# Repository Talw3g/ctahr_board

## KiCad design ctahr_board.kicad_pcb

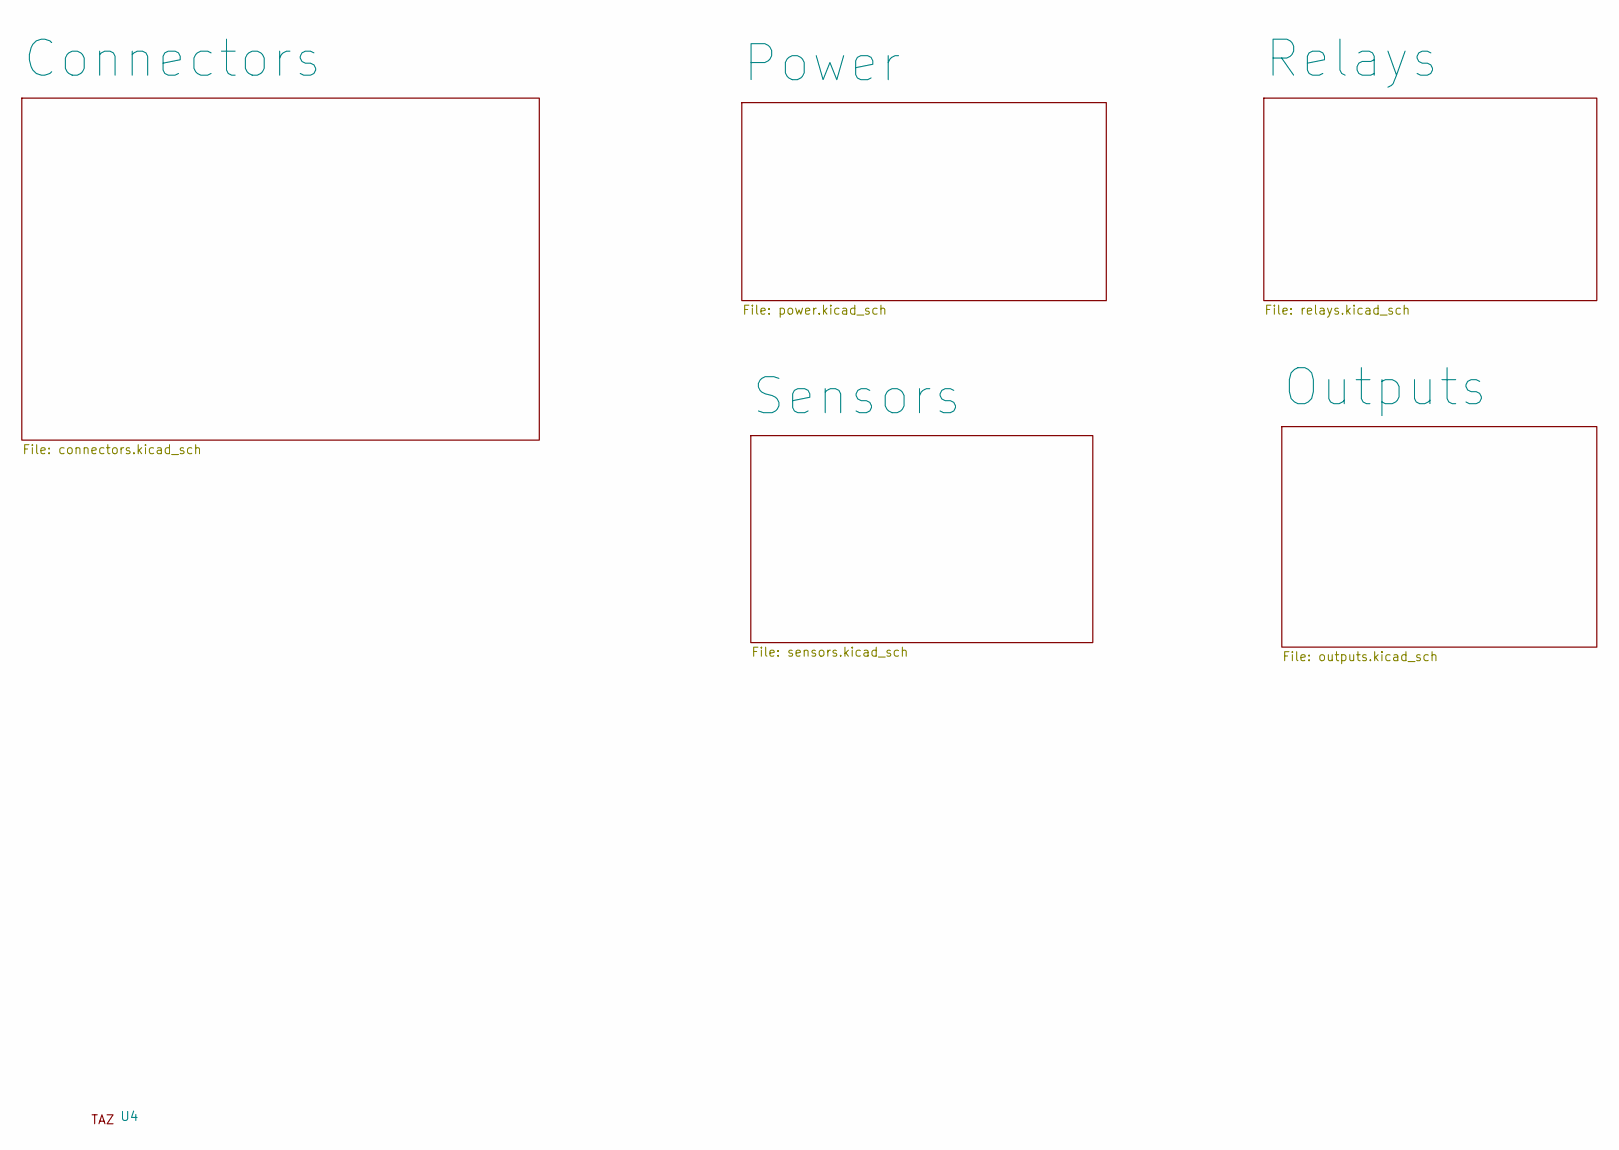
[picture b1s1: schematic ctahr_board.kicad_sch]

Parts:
U4: taz

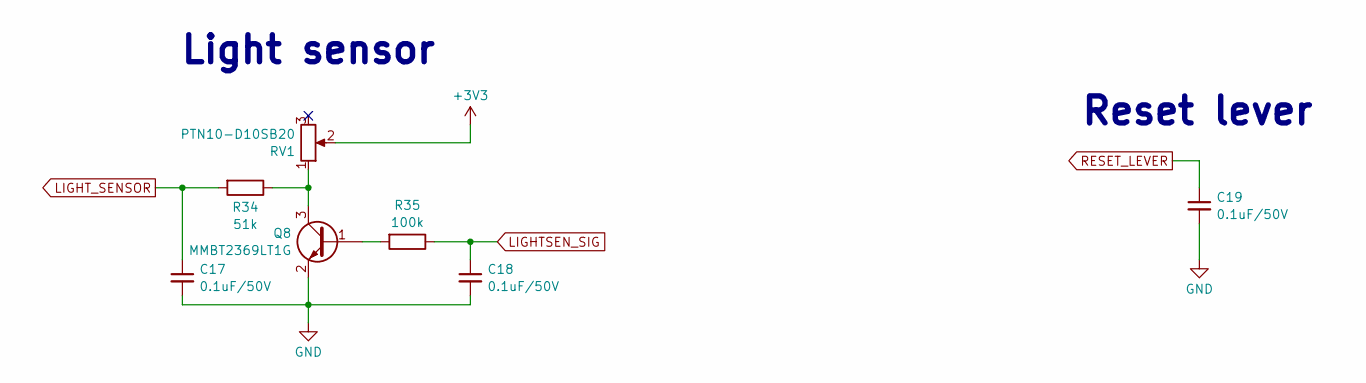
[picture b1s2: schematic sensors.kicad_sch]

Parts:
C17, C18, C19: 0.1uF/50V; C_0603_1608Metric_Pad1.08x0.95mm_HandSolder
Q8: MMBT2369LT1G; SOT-23_Handsoldering
R34: 51k; R_0603_1608Metric_Pad0.98x0.95mm_HandSolder
R35: 100k; R_0603_1608Metric_Pad0.98x0.95mm_HandSolder
RV1: PTN10-D10SB20; TRIM_PTN10-D10SB20

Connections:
+3V3: RV1.2; also elsewhere on the board
GND: C17.2, C18.2, C19.2, Q8.2 (E); also elsewhere on the board
LIGHTSEN_SIG: C18.1, R35.1; also elsewhere on the board
LIGHT_SENSOR: C17.1, R34.2; also elsewhere on the board
unnamed: Q8.1 (B), R35.2
unnamed: Q8.3 (C), R34.1, RV1.1
RESET_LEVER: C19.1; also elsewhere on the board

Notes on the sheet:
Reset lever
Light sensor

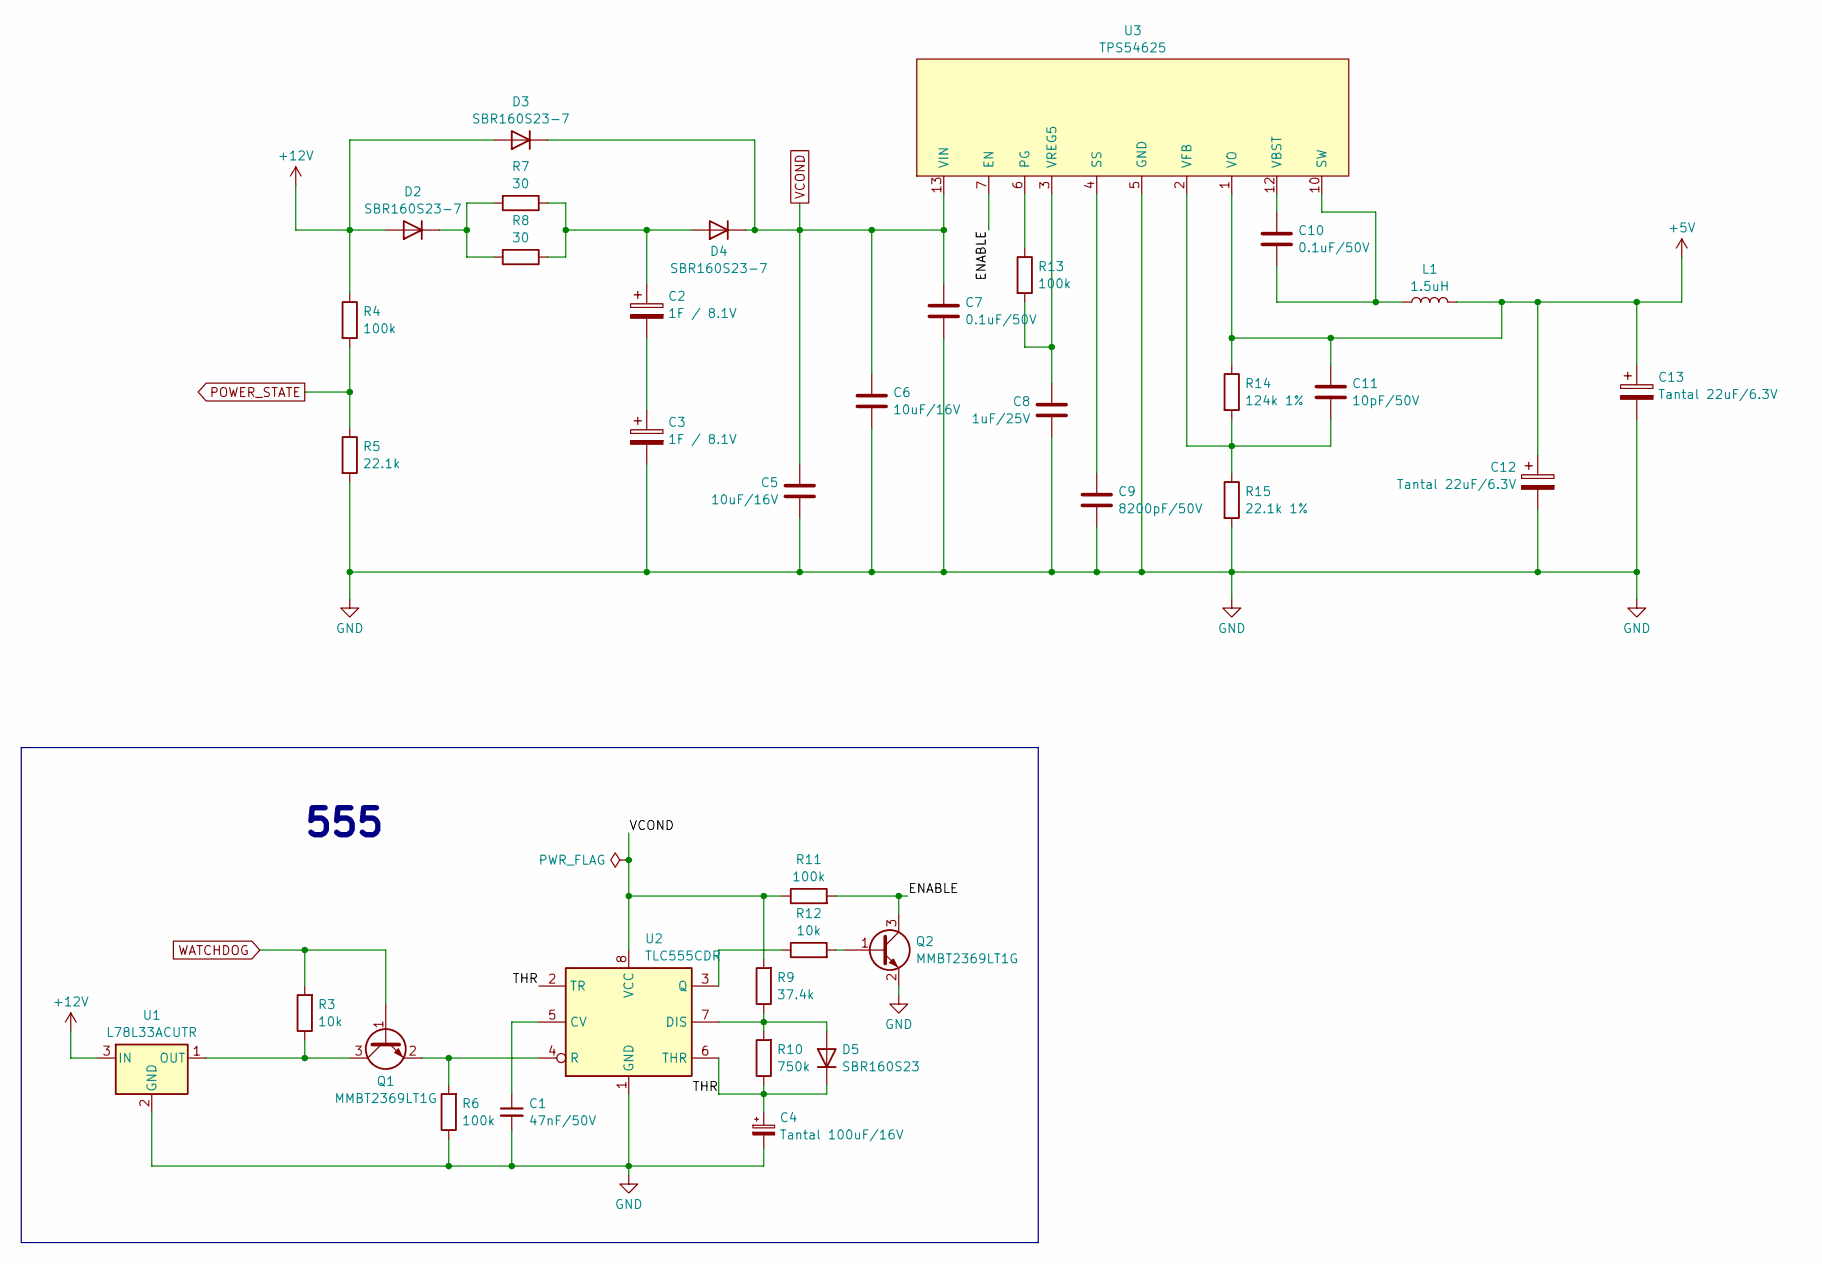
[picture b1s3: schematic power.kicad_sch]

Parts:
C1: 47nF/50V; C_0603_1608Metric_Pad1.08x0.95mm_HandSolder
C2, C3: 1F / 8.1V; SCMR22G105SRBA0_vertical; Farnell 2856949
C4: Tantal 100uF/16V; CP_EIA-7343-30_AVX-N_Pad2.25x2.55mm_HandSolder
C5, C6: 10uF/16V; C_0805_2012Metric_Pad1.18x1.45mm_HandSolder
C7, C10: 0.1uF/50V; C_0603_1608Metric_Pad1.08x0.95mm_HandSolder
C8: 1uF/25V; C_0603_1608Metric_Pad1.08x0.95mm_HandSolder
C9: 8200pF/50V; C_0603_1608Metric_Pad1.08x0.95mm_HandSolder
C11: 10pF/50V; C_0603_1608Metric_Pad1.08x0.95mm_HandSolder
C12, C13: Tantal 22uF/6.3V; CP_EIA-3216-10_Kemet-I_Pad1.58x1.35mm_HandSolder; Farnell 2321204
D2, D3, D4: SBR160S23-7; SBR160S23; Farnell 1863724
D5: SBR160S23
L1: 1.5uH; L_7.1x6.5_H3; Farnell 2215610
Q1, Q2: MMBT2369LT1G; SOT-23_Handsoldering
R3, R12: 10k; R_0603_1608Metric_Pad0.98x0.95mm_HandSolder
R4, R6, R11, R13: 100k; R_0603_1608Metric_Pad0.98x0.95mm_HandSolder
R5: 22.1k; R_0603_1608Metric_Pad0.98x0.95mm_HandSolder
R7, R8: 30; TE_SM5; Farnell 2331667
R9: 37.4k; R_0603_1608Metric_Pad0.98x0.95mm_HandSolder
R10: 750k; R_0603_1608Metric_Pad0.98x0.95mm_HandSolder
R14: 124k 1%; R_0603_1608Metric_Pad0.98x0.95mm_HandSolder
R15: 22.1k 1%; R_0603_1608Metric_Pad0.98x0.95mm_HandSolder
U1: L78L33ACUTR; SOT-89-3_Handsoldering
U2: TLC555CDR; SOIC-8_3.9x4.9mm_P1.27mm
U3: TPS54625; HTSSOP-14-PWP_Handsolder

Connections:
+5V: C11.1, C12.1, C13.1, L1.2, R14.1, U3.1 (VO); also elsewhere on the board
+12V: D2.2 (A), D3.2 (A), R4.1, U1.3 (IN); also elsewhere on the board
/Power/ENABLE: Q2.3 (C), R11.2, U3.7 (EN)
/Power/THR: C4.1, D5.1 (K), R10.1, U2.2 (TR), U2.6 (THR)
GND: C1.2, C3.2, C4.2, C5.2, C6.2, C7.2, C8.2, C9.2, C12.2, C13.2, Q2.2 (E), R5.2, R6.1, R15.2, U1.2 (GND), U2.1 (GND), U3.5 (GND), U3.8 (GND), U3.9 (GND), U3.15 (GND); also elsewhere on the board
unnamed: C2.2, C3.1
unnamed: C10.2, L1.1, U3.10 (SW), U3.11 (SW)
unnamed: D2.1 (K), R7.2, R8.2
unnamed: C2.1, D4.2 (A), R7.1, R8.1
unnamed: D5.2 (A), R9.1, R10.2, U2.7 (DIS)
unnamed: Q1.3 (C), R3.1, U1.1 (OUT)
unnamed: Q1.2 (E), R6.2, U2.4 (R)
unnamed: Q2.1 (B), R12.2
unnamed: C1.1, U2.5 (CV)
unnamed: R12.1, U2.3 (Q)
unnamed: R13.1, U3.6 (PG)
unnamed: C9.1, U3.4 (SS)
unnamed: C10.1, U3.12 (VBST)
unnamed: C11.2, R14.2, R15.1, U3.2 (VFB)
unnamed: C8.1, R13.2, U3.3 (VREG5)
POWER_STATE: R4.2, R5.1; also elsewhere on the board
VCOND: C5.1, C6.1, C7.1, D3.1 (K), D4.1 (K), R9.2, R11.1, U2.8 (VCC), U3.13 (VIN), U3.14 (VIN)
WATCHDOG: Q1.1 (B), R3.2; also elsewhere on the board

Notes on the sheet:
555

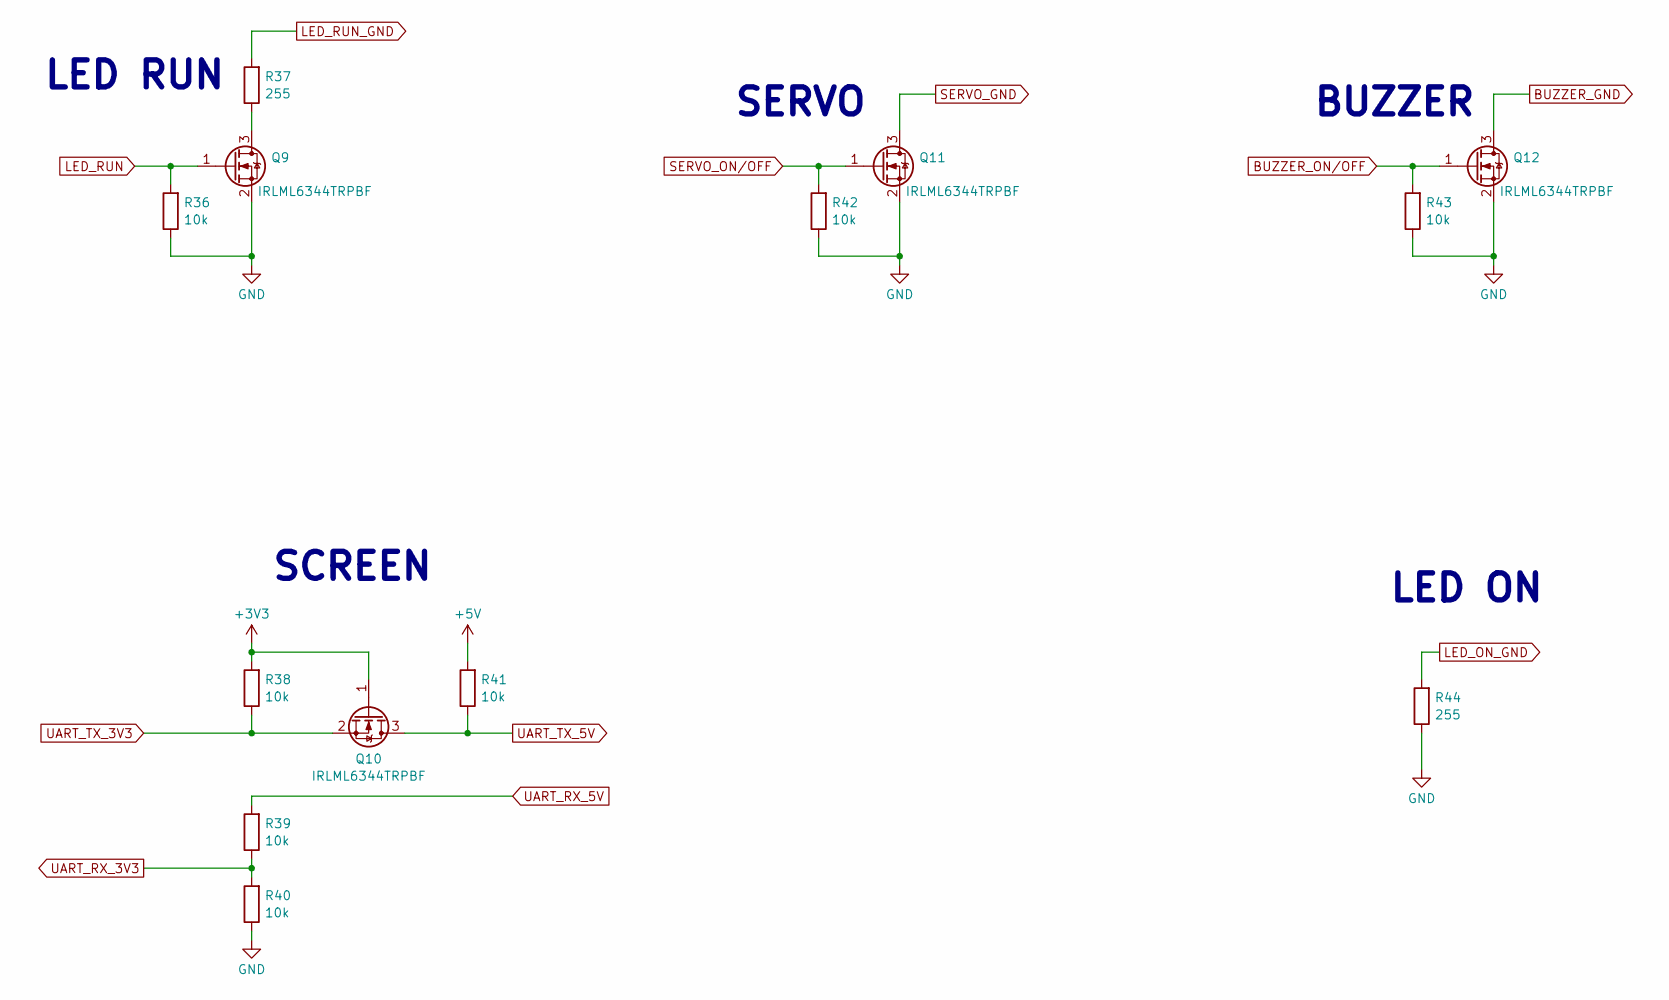
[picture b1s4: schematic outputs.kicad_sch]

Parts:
Q9, Q10, Q11, Q12: IRLML6344TRPBF; SOT-23_Handsoldering
R36, R38, R39, R40, R41, R42, R43: 10k; R_0603_1608Metric_Pad0.98x0.95mm_HandSolder
R37, R44: 255; R_0603_1608Metric_Pad0.98x0.95mm_HandSolder

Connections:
+3V3: Q10.1 (G), R38.2; also elsewhere on the board
+5V: R41.2; also elsewhere on the board
BUZZER_GND: Q12.3 (D); also elsewhere on the board
BUZZER_ON/OFF: Q12.1 (G), R43.2; also elsewhere on the board
GND: Q9.2 (S), Q11.2 (S), Q12.2 (S), R36.1, R40.1, R42.1, R43.1, R44.1; also elsewhere on the board
LED_ON_GND: R44.2; also elsewhere on the board
LED_RUN: Q9.1 (G), R36.2; also elsewhere on the board
LED_RUN_GND: R37.2; also elsewhere on the board
unnamed: Q9.3 (D), R37.1
SERVO_GND: Q11.3 (D); also elsewhere on the board
SERVO_ON/OFF: Q11.1 (G), R42.2; also elsewhere on the board
UART_RX_3V3: R39.1, R40.2; also elsewhere on the board
UART_RX_5V: R39.2; also elsewhere on the board
UART_TX_3V3: Q10.2 (S), R38.1; also elsewhere on the board
UART_TX_5V: Q10.3 (D), R41.1; also elsewhere on the board

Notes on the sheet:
LED ON
LED RUN
SCREEN
SERVO
BUZZER

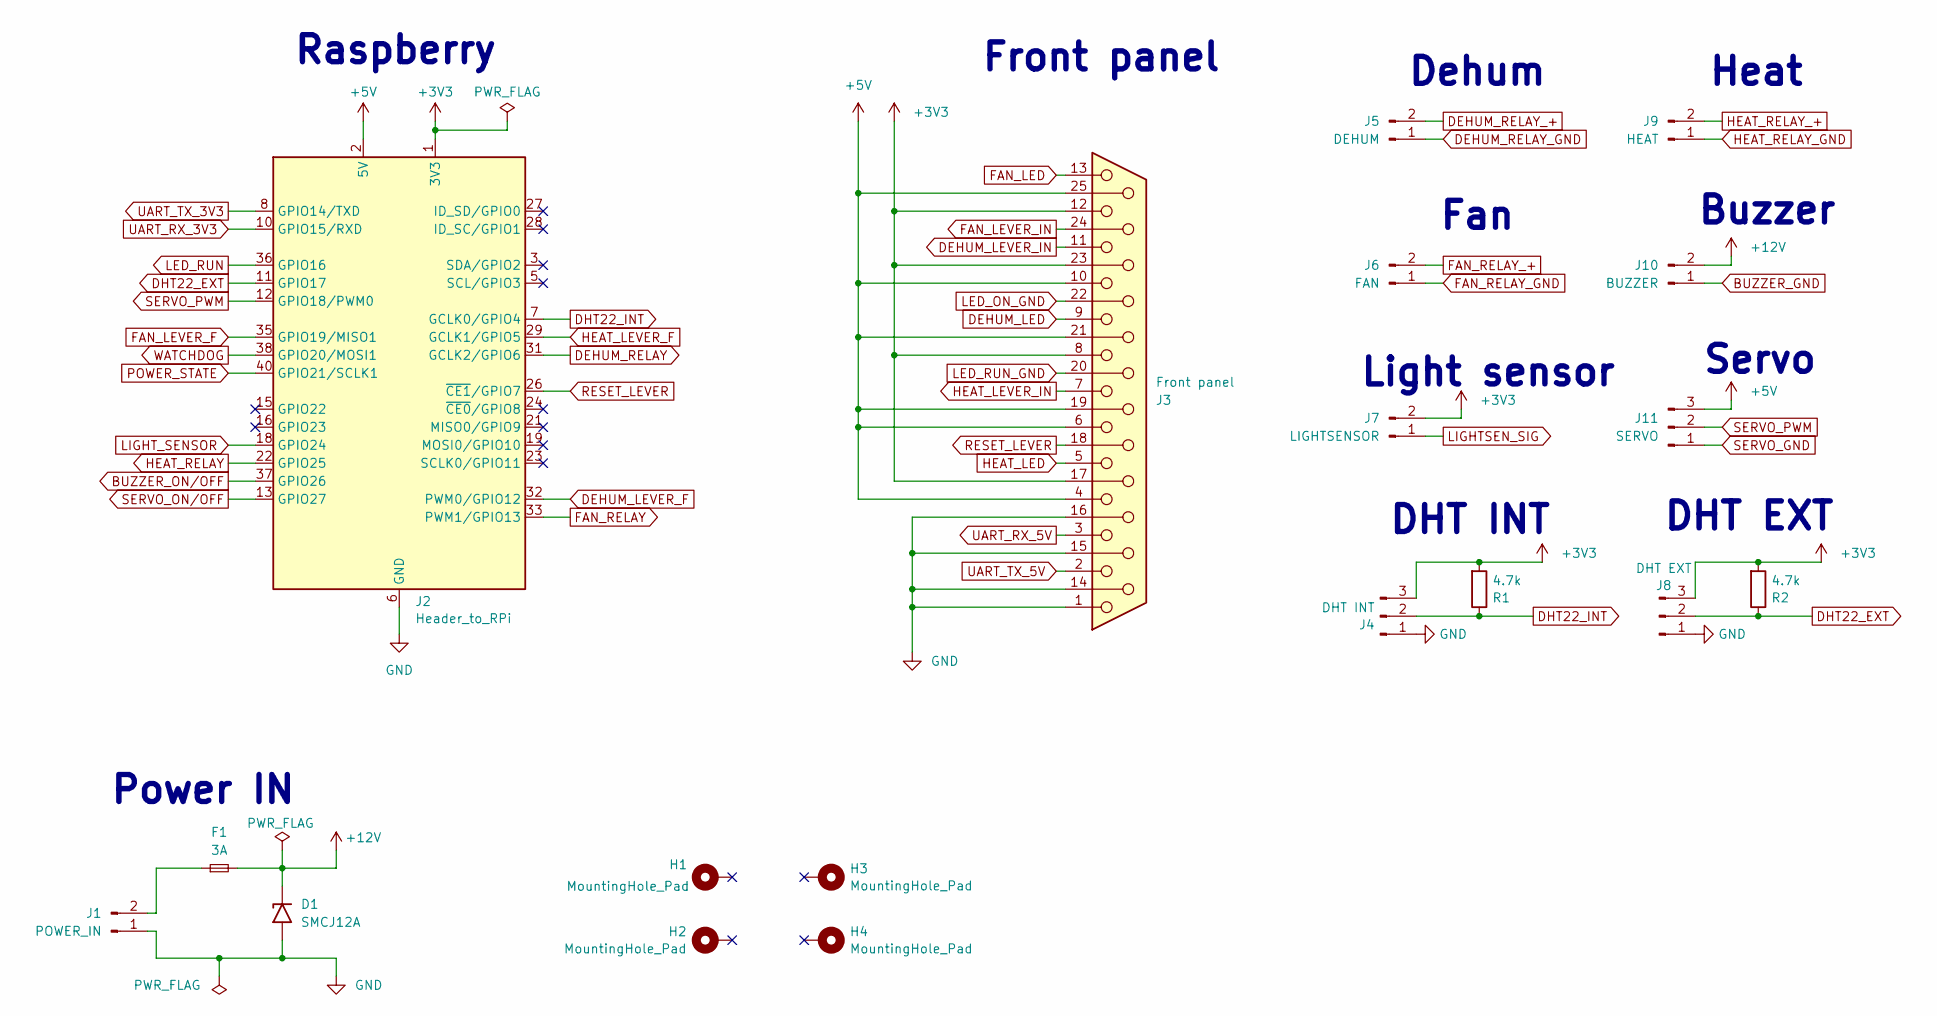
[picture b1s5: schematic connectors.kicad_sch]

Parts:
D1: SMCJ12A; D_SMC_Handsoldering
F1: 3A; Fuseholder_Littelfuse_Nano2_154x
H1, H2, H3, H4: MountingHole_Pad; MountingHole_2.2mm_M2_ISO14580_Pad_TopBottom
J1: POWER_IN; JST_XH_B2B-XH-A_1x02_P2.50mm_Vertical
J2: Header_to_RPi; PinHeader_2x20_P2.54mm_Vertical
J3: Front panel; DSUB-25_Female_Vertical_P2.77x2.84mm
J4: DHT INT; JST_XH_B3B-XH-A_1x03_P2.50mm_Vertical
J5: DEHUM; JST_XH_B2B-XH-A_1x02_P2.50mm_Vertical
J6: FAN; JST_XH_B2B-XH-A_1x02_P2.50mm_Vertical
J7: LIGHTSENSOR; JST_XH_B2B-XH-A_1x02_P2.50mm_Vertical
J8: DHT EXT; JST_XH_B3B-XH-A_1x03_P2.50mm_Vertical
J9: HEAT; JST_XH_B2B-XH-A_1x02_P2.50mm_Vertical
J10: BUZZER; JST_XH_B2B-XH-A_1x02_P2.50mm_Vertical
J11: SERVO; JST_XH_B3B-XH-A_1x03_P2.50mm_Vertical
R1, R2: 4.7k; R_0603_1608Metric_Pad0.98x0.95mm_HandSolder

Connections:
+3V3: J2.1 (3V3), J2.17 (3V3), J3.8, J3.12, J3.17, J3.23, J4.3, J7.2, J8.3, R1.2, R2.2; also elsewhere on the board
+5V: J2.2 (5V), J2.4 (5V), J3.4, J3.6, J3.10, J3.19, J3.21, J3.25, J11.3; also elsewhere on the board
+12V: D1.1 (A1), F1.2, J10.2; also elsewhere on the board
BUZZER_GND: J10.1; also elsewhere on the board
BUZZER_ON/OFF: J2.37 (GPIO26); also elsewhere on the board
DEHUM_LED: J3.9; also elsewhere on the board
DEHUM_LEVER_F: J2.32 (PWM0/GPIO12); also elsewhere on the board
DEHUM_LEVER_IN: J3.11; also elsewhere on the board
DEHUM_RELAY: J2.31 (GCLK2/GPIO6); also elsewhere on the board
DEHUM_RELAY_+: J5.2; also elsewhere on the board
DEHUM_RELAY_GND: J5.1; also elsewhere on the board
DHT22_EXT: J2.11 (GPIO17), J8.2, R2.1
DHT22_INT: J2.7 (GCLK0/GPIO4), J4.2, R1.1
FAN_LED: J3.13; also elsewhere on the board
FAN_LEVER_F: J2.35 (GPIO19/MISO1); also elsewhere on the board
FAN_LEVER_IN: J3.24; also elsewhere on the board
FAN_RELAY: J2.33 (PWM1/GPIO13); also elsewhere on the board
FAN_RELAY_+: J6.2; also elsewhere on the board
FAN_RELAY_GND: J6.1; also elsewhere on the board
GND: D1.2 (A2), J1.1, J2.6 (GND), J2.9 (GND), J2.14 (GND), J2.20 (GND), J2.25 (GND), J2.30 (GND), J2.34 (GND), J2.39 (GND), J3.1, J3.14, J3.15, J3.16, J4.1, J8.1; also elsewhere on the board
HEAT_LED: J3.5; also elsewhere on the board
HEAT_LEVER_F: J2.29 (GCLK1/GPIO5); also elsewhere on the board
HEAT_LEVER_IN: J3.7; also elsewhere on the board
HEAT_RELAY: J2.22 (GPIO25); also elsewhere on the board
HEAT_RELAY_+: J9.2; also elsewhere on the board
HEAT_RELAY_GND: J9.1; also elsewhere on the board
LED_ON_GND: J3.22; also elsewhere on the board
LED_RUN: J2.36 (GPIO16); also elsewhere on the board
LED_RUN_GND: J3.20; also elsewhere on the board
LIGHTSEN_SIG: J7.1; also elsewhere on the board
LIGHT_SENSOR: J2.18 (GPIO24); also elsewhere on the board
unnamed: F1.1, J1.2
POWER_STATE: J2.40 (GPIO21/SCLK1); also elsewhere on the board
RESET_LEVER: J2.26 (~CE1/GPIO7), J3.18; also elsewhere on the board
SERVO_GND: J11.1; also elsewhere on the board
SERVO_ON/OFF: J2.13 (GPIO27); also elsewhere on the board
SERVO_PWM: J2.12 (GPIO18/PWM0), J11.2
UART_RX_3V3: J2.10 (GPIO15/RXD); also elsewhere on the board
UART_RX_5V: J3.3; also elsewhere on the board
UART_TX_3V3: J2.8 (GPIO14/TXD); also elsewhere on the board
UART_TX_5V: J3.2; also elsewhere on the board
WATCHDOG: J2.38 (GPIO20/MOSI1); also elsewhere on the board

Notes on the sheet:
Buzzer
DHT INT
Front panel
Power IN
Heat
DHT EXT
Dehum
Fan
Servo
Light sensor
Raspberry

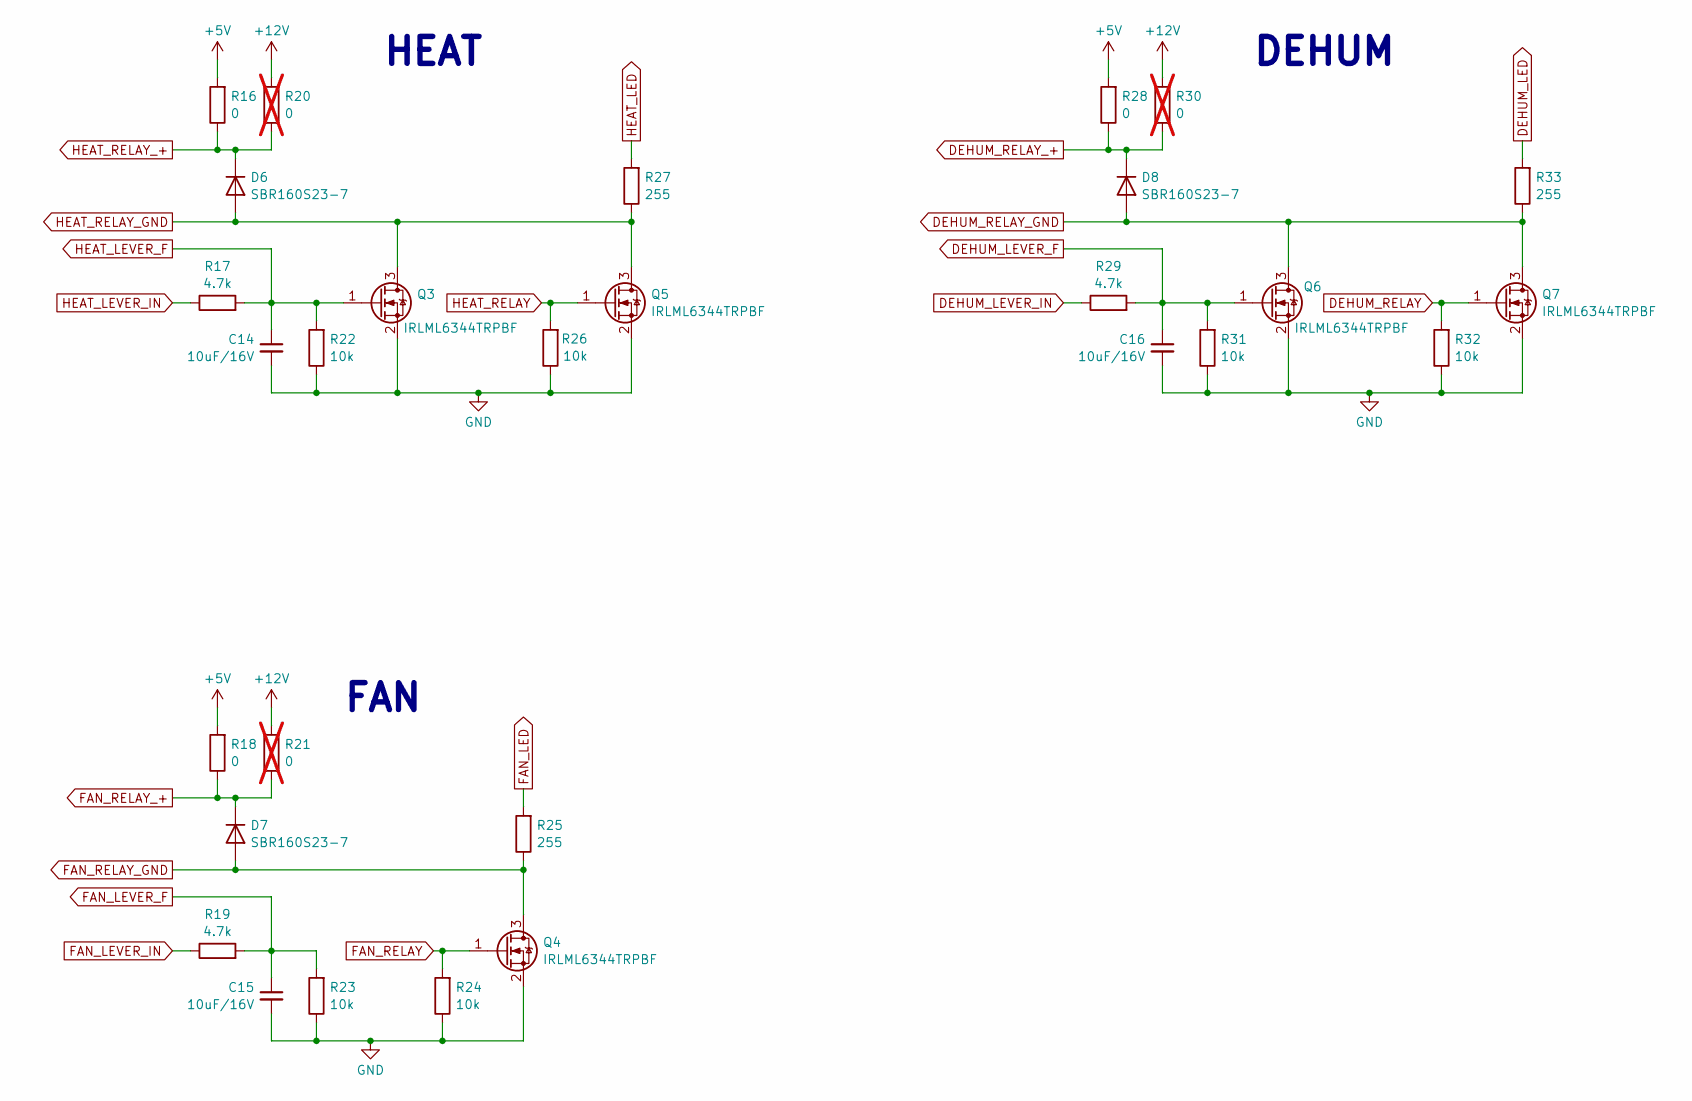
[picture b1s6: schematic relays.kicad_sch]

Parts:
C14, C15, C16: 10uF/16V; C_0805_2012Metric_Pad1.18x1.45mm_HandSolder
D6, D7, D8: SBR160S23-7; SBR160S23; Farnell 1863724
Q3, Q4, Q5, Q6, Q7: IRLML6344TRPBF; SOT-23_Handsoldering
R16, R18, R28: 0; R_0603_1608Metric_Pad0.98x0.95mm_HandSolder
R17, R19, R29: 4.7k; R_0603_1608Metric_Pad0.98x0.95mm_HandSolder
R20, R21, R30: 0; R_0603_1608Metric_Pad0.98x0.95mm_HandSolder; not fitted
R22, R23, R24, R26, R31, R32: 10k; R_0603_1608Metric_Pad0.98x0.95mm_HandSolder
R25, R27, R33: 255; R_0603_1608Metric_Pad0.98x0.95mm_HandSolder

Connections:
+5V: R16.2, R18.2, R28.2; also elsewhere on the board
+12V: R20.2, R21.2, R30.2; also elsewhere on the board
DEHUM_LED: R33.2; also elsewhere on the board
DEHUM_LEVER_F: C16.1, Q6.1 (G), R29.2, R31.2; also elsewhere on the board
DEHUM_LEVER_IN: R29.1; also elsewhere on the board
DEHUM_RELAY: Q7.1 (G), R32.2; also elsewhere on the board
DEHUM_RELAY_+: D8.1 (K), R28.1, R30.1; also elsewhere on the board
DEHUM_RELAY_GND: D8.2 (A), Q6.3 (D), Q7.3 (D), R33.1; also elsewhere on the board
FAN_LED: R25.2; also elsewhere on the board
FAN_LEVER_F: C15.1, R19.2, R23.2; also elsewhere on the board
FAN_LEVER_IN: R19.1; also elsewhere on the board
FAN_RELAY: Q4.1 (G), R24.2; also elsewhere on the board
FAN_RELAY_+: D7.1 (K), R18.1, R21.1; also elsewhere on the board
FAN_RELAY_GND: D7.2 (A), Q4.3 (D), R25.1; also elsewhere on the board
GND: C14.2, C15.2, C16.2, Q3.2 (S), Q4.2 (S), Q5.2 (S), Q6.2 (S), Q7.2 (S), R22.1, R23.1, R24.1, R26.1, R31.1, R32.1; also elsewhere on the board
HEAT_LED: R27.2; also elsewhere on the board
HEAT_LEVER_F: C14.1, Q3.1 (G), R17.2, R22.2; also elsewhere on the board
HEAT_LEVER_IN: R17.1; also elsewhere on the board
HEAT_RELAY: Q5.1 (G), R26.2; also elsewhere on the board
HEAT_RELAY_+: D6.1 (K), R16.1, R20.1; also elsewhere on the board
HEAT_RELAY_GND: D6.2 (A), Q3.3 (D), Q5.3 (D), R27.1; also elsewhere on the board

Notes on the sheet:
FAN
HEAT
DEHUM

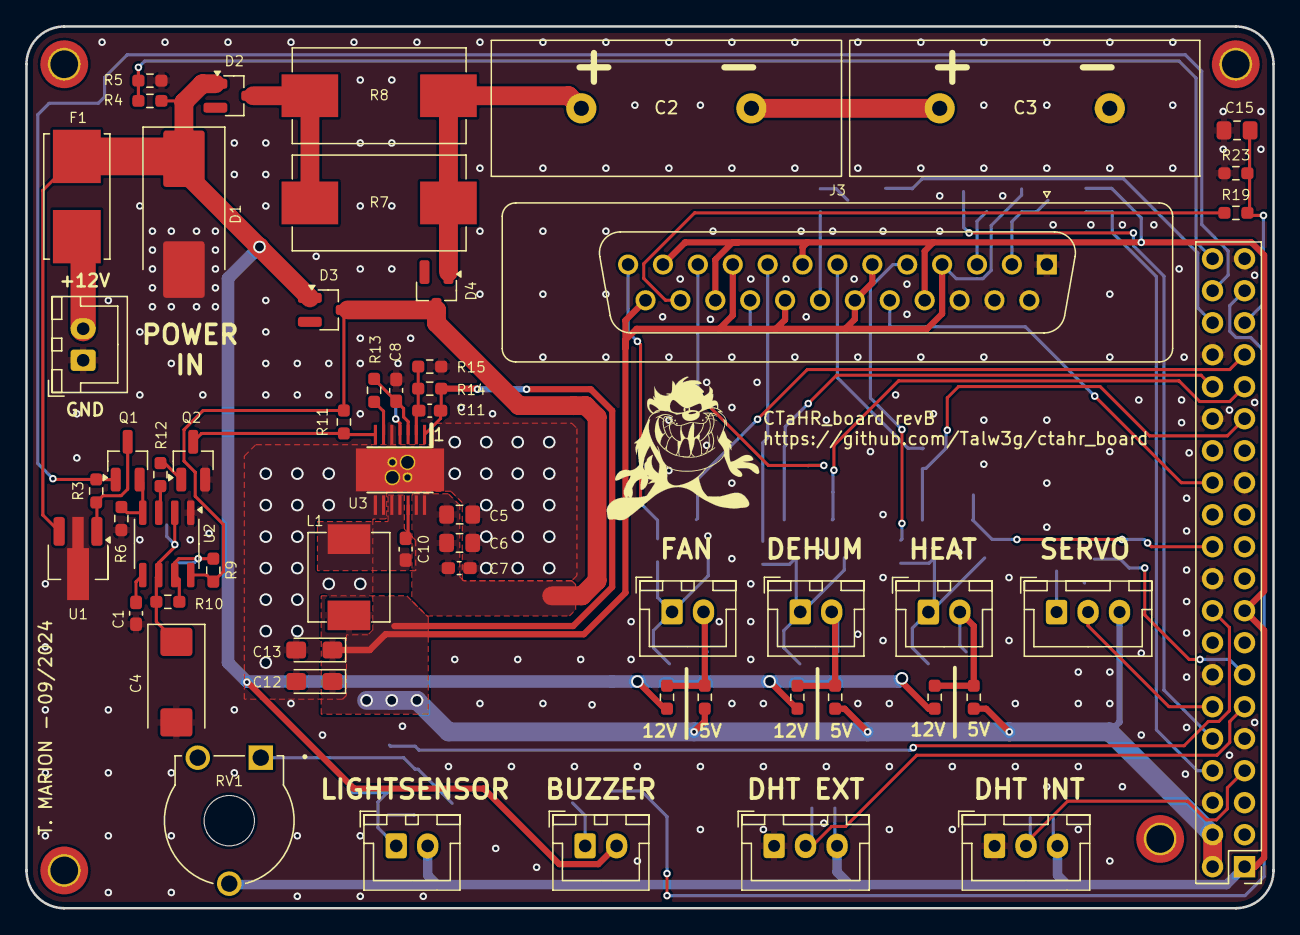
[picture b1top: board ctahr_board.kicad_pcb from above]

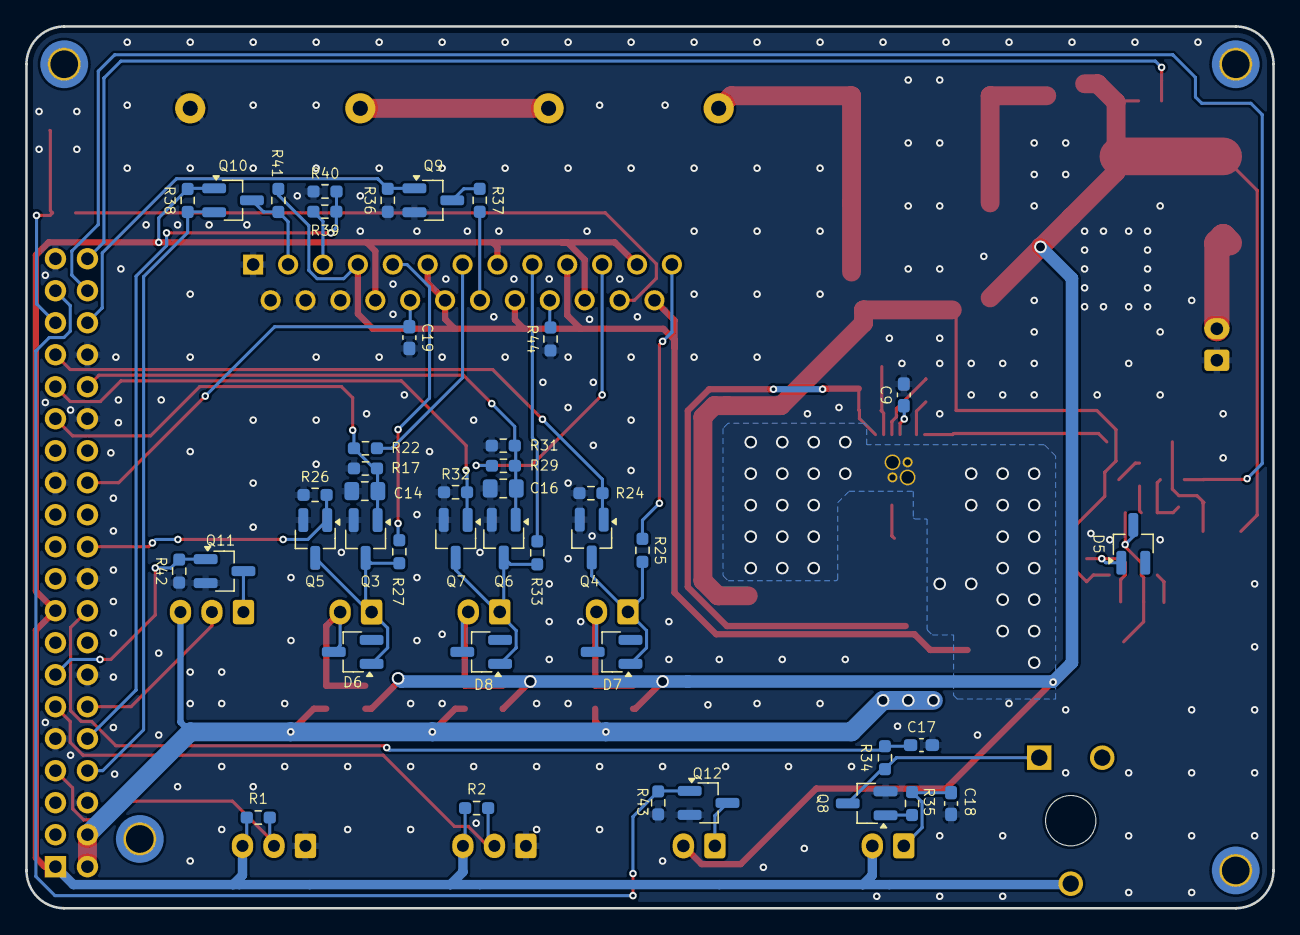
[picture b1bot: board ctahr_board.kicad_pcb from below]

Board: 2 copper layers, 99.0 x 70.0 mm, 105 parts (43 on the bottom side), 63 nets.

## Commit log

2024-08-26 Corrected gitignore
2024-08-27 Connectors for RPi and front panel done (sch)
2024-08-27 Connectors done, WIP on power
2024-08-28 Added power surge protection
2024-08-29 Schematic done (for now), WIP on layout
2024-08-30 WIP on layout
2024-08-31 Routing done, need to work on silkscreen
2024-09-01 All done, pending review
